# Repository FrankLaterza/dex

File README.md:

# Dex
An open source self balancing robot designed for the Raspberry Pi Pico and controlled by a DS4 controller. Dex was made with 3D printed ABS, a custom PCB, and a whole lot of patience. This repository shall serve as a reference for anyone making their own balancing robot. The code is well formatted for your convenience you nerd. Note this is an intermediate project so take your time and have fun.

<div style="display:flex; justify-content:center;">
  
</div>
<br/>

## Software
This project uses the several libraries including FreeRTOS, BTstack, and the Pico SDK. Each is a specific versions and can be setup with a recursive git clone. For this project the software utilizes both cores on the RP2040.
_
### Core 0
The primary purpose of core 0 is to handle all of the CWY43 SPI and MPU6050 I2C interrupts that hog all the cpu.

### Core 1
The FreeRTOS scheduler runs on this core to prevent conflicting timing with the SPI interrupted. The bluetooth callback also gets processed here. 

| FreeRTOS Scheduler Tasks | Description | Task Delay us |
| ----- | ---- | ---- |
| stat_led_task | blinky blinky | 500000us |
| bt_hid_inputs | process controller inputs | 20000us |
| stepper_left_task | controls the left stepper | varying per step |
| stepper_right_task | controls the right stepper | varying per step  |
| mpu6050_task | requests gyro/accelerometer data and processed roll angle with Kalman filter | 20000us |
| pid_task | calculates the output for the stepper motors | 10000us |
| good_boy_task | watches the dog | 500000us |

### Overclocking
Please note this project overclock the RP2040 to 250MHz and configures the configTICK_RATE_HZ 100000 (10us period). This is to give enough time for the schedule overhead. The reason for the high tick rate is because the steppers need step at very high rates.

## PCB 
This PCB was made in Eagle Cad and can find the PCB under resources/pcb. Please note there are two mistakes that i've hand wired for this current pcb. The holes for the switch are too small and cut traces to make the switch come before the 5V regulator. I'll update the files with a fixed design soon.

<div style="display:flex; justify-content:center;">
  
</div>

## CAD
This project was designed in Fusion 360 and all the files can be found under resources/cad. 
<div style="display:flex; justify-content:center;">
  
</div>

## BOM 💣

| Name                    | Count | Price (meets count) | Description                               | Rating                   | Notes                                        | Link                                                                                                                             |
|-------------------------|-------|----------------------|-------------------------------------------|--------------------------|----------------------------------------------|-----------------------------------------------------------------------------------------------------------------------------------|
| Raspberry Pi PIco W      | 1     | $18.96               | MPU                                       | Clock: 135MHz            | 2 Cores                                      | [Amazon Link](https://www.amazon.com/gp/product/B0B72GV3K3/ref=ewc_pr_img_12?smid=A1PI3LRUETBKN8&psc=1)                            |
| PCB                     | 1     | $24.05               | Custom PCB designed                        | Engineering Level: Maximum | Designed in Eagle and order on JLCPCB        | N/A                                                                                                                               |
| NEMA 17 Stepper         | 2     | $13.99               | Main Motors                                | Max Current 2a           |                                              | [Amazon Link](https://www.amazon.com/gp/product/B0B72GV3K3/ref=ewc_pr_img_12?smid=A1PI3LRUETBKN8&psc=1)                            |
| Stepper Driver A4988    | 2     | $14.99               | Drives the stepper motors                  | Min Step Rate: 500kHz    |                                              | [Amazon Link](https://www.amazon.com/gp/product/B09X382335/ref=ewc_pr_img_2?smid=A1VTL661FOEJB1&th=1)                            |
| MPU-6050                | 1     | $7.59                | 3 Axis Gryo and Accelerometer               | 16bit                    |                                              | [Amazon Link](https://www.amazon.com/gp/product/B0B3D6D1KD/ref=ppx_yo_dt_b_search_asin_title?ie=UTF8&psc=1)                      |
| L7805CV                 | 1     | $8.59                | 5V Voltage Regulator                       | 35Vin and 5Vout/1.5A     |                                              | [Amazon Link](https://www.amazon.com/gp/product/B0CBKCDT4H/ref=ewc_pr_img_1?smid=A3FX7C4A9P37IQ&th=1)                             |
| Power Switch            | 1     | $6.99                | AC 125V 2A                                 |                          | Only cuts power 5V power not stepper input voltage | [Amazon Link](https://www.amazon.com/gp/product/B099N61GTZ/ref=ewc_pr_img_3?smid=A3KX1QBS9AS0L7&th=1)                              |
| LED                     | 4     | $11.99               |                                           | Forward Voltage: R/Y 2.0-2.2V; B/G/W 3.0-3.2V; Max. Current: 20mA | User about 100Ohm resistor                | [Amazon Link](https://www.amazon.com/DiCUNO-450pcs-Colors-Emitting-Assorted/dp/B073QMYKDM/ref=sr_1_3?crid=25RYXUCKOI5YQ&keywords=led+5mm&qid=1702651386&s=hi&sprefix=led+5mm%2Ctools%2C109&sr=1-3) |
| Beeper                  | 1     | $7.99                | Active beeeper                             | 2.5-4V/25mA.             | Make sure to be extra annoying                   | [Amazon Link](https://www.amazon.com/gp/product/B07VRK7ZPF/ref=ewc_pr_img_5?smid=A10PG8DP5LW0Q1&psc=1)                           |
| Resistors               | 4     | $5.99                | Resistor for LEDS                          |                          |                                              | [Amazon Link](https://www.amazon.com/MCIGICM-Values-Resistor-Assortment-Resistors/dp/B06WRQS97C/ref=sr_1_3?crid=1DUTLH3JED9NZ&keywords=resistor+pack&qid=1702651595&s=electronics&sprefix=resistor+pack%2Celectronics%2C136&sr=1-3) |
| Headers                 | N/A   | $7.99                | Used for PCB and IO                        |                          |                                              | [Amazon Link](https://www.amazon.com/2-54mm-Breakaway-Female-Connector-Arduino/dp/B01MQ48T2V/ref=sr_1_3?crid=3A3SUEBT5HOUP&keywords=headers%2Bmale%2Band%2Bfemale&qid=1702651771&sprefix=headers%2Bmale%2Band%2Bfemail%2B%2Caps%2C112&sr=8-3&th=1) |
| Battery                 | 1     | $44.99               | Any 4s Lipo will work                     | 4S Lipo Battery 5200mAh 14.8V 60C |                                              | [Amazon Link](https://www.amazon.com/Pairs-Connector-Female-Silicon-Battery/dp/B07QM1WS2J/ref=sr_1_6?crid=2MAGLONAR29QX&keywords=Dean+t+plug&qid=1702651946&s=toys-and-games&sprefix=dean+t+plu%2Ctoys-and-games%2C98&sr=1-6) |
| O rings                 | 2     | $5.99                | Goes over 3d printed wheel for grip        | 110mm OD 100mm ID 5mm Width | I used the wheels from Wouter [here](https://elexperiment.nl/2018/11/high-speed-balancing-robot-introduction/)             | [Amazon Link](https://www.amazon.com/gp/product/B07GXFKGNT/ref=ppx_yo_dt_b_search_asin_title?ie=UTF8&th=1)                       |
| 3D Printed Chassis       | 1     | 0                    | Main body of the robot                     |                          | Designed in Fusion 360                         | N/A                                                                |
| 3D printed Wheels       | 2     | 0                    | Main wheels with rubber O rings            | Designed in Fusion 360 CREDIT DESIGN |                                           | N/A                                                            |

## Known Issues
* Sometimes the program will halt when trying to connect to the BT HID.
* Cannot reconnect to pico after pair to another controller.

## Starting Debugger
Plug in debugger and run:
```
openocd -f interface/cmsis-dap.cfg -c "adapter speed 5000" -f target/rp2040.cfg -s tcl
```
confrim this starts on localhost:3333

open another terminal and run:
```
gdb-multiarch dex.elf
```
in this termincal type the command
```
target remote localhost:3333
```
load with 
```
load
```

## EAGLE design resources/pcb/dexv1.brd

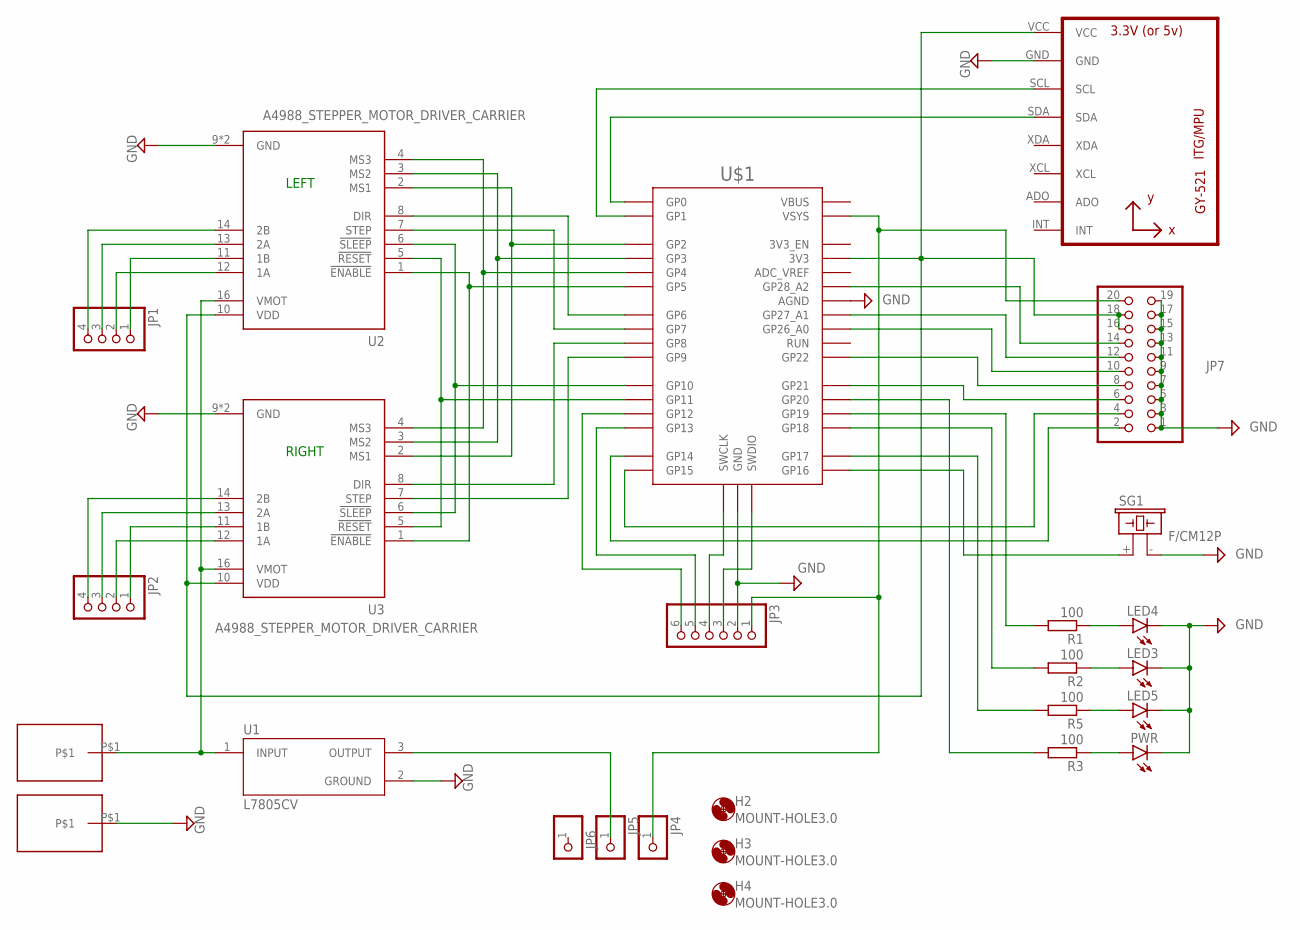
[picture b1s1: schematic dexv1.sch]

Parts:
H2, H3, H4: MOUNT-HOLE3.0; 3,0
JP1, JP2: PINHD-1X4; 1X04
JP3: PINHD-1X6; 1X06
JP4, JP5, JP6: PINHD-1X1; 1X01
JP7: PINHD-2X10; 2X10
LED3, LED4, LED5: LED5MM
PWR: LED5MM
R1, R2, R3, R5: 100; 0204/7
SG1: F/CM12P
U1: L7805CV; TO255P1040X460X1968-3
U2, U3: A4988_STEPPER_MOTOR_DRIVER_CARRIER; MODULE_A4988_STEPPER_MOTOR_DRIVER_CARRIER
U4: GY-521MPU6050; GY-521
U$1: RPI_PICO-TH; RPI_PICO_TH
U$2, U$3: SMD5X10

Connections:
GND: JP3.2, JP7.1, JP7.3, JP7.5, JP7.7, JP7.9, JP7.11, JP7.13, JP7.15, JP7.17, JP7.19, LED3.K (C), LED4.K (C), LED5.K (C), PWR.K (C), SG1.- (2), U1.2 (GROUND), U2.9 (GND), U2.15 (GND), U3.9 (GND), U3.15 (GND), U4.GND, U$1.AGND, U$1.GND@1 (GND), U$1.GND@2 (GND), U$1.GND@3 (GND), U$1.GND@4 (GND), U$1.GND@5 (GND), U$1.GND@6 (GND), U$1.GND@7 (GND), U$1.GND@8 (GND), U$1.P$2 (GND), U$3.P$1
unnamed: JP2.2, U3.12 (1A)
unnamed: U4.SDA, U$1.GP0
unnamed: JP7.14, U$1.GP28_A2
unnamed: U2.4 (MS3), U3.4 (MS3), U$1.GP4
unnamed: U2.3 (MS2), U3.3 (MS2), U$1.GP3
unnamed: U2.2 (MS1), U3.2 (MS1), U$1.GP2
unnamed: U2.8 (DIR), U$1.GP6
unnamed: U2.7 (STEP), U$1.GP7
unnamed: U3.8 (DIR), U$1.GP8
unnamed: U2.1 (!ENABLE), U3.1 (!ENABLE), U$1.GP5
unnamed: U3.7 (STEP), U$1.GP9
unnamed: U2.6 (!SLEEP), U3.6 (!SLEEP), U$1.GP10
unnamed: U2.5 (!RESET), U3.5 (!RESET), U$1.GP11
unnamed: JP1.2, U2.12 (1A)
unnamed: JP1.1, U2.11 (1B)
unnamed: JP1.3, U2.13 (2A)
unnamed: JP1.4, U2.14 (2B)
unnamed: JP2.1, U3.11 (1B)
unnamed: JP2.3, U3.13 (2A)
unnamed: JP2.4, U3.14 (2B)
unnamed: JP3.1, JP4.1, JP7.20, U$1.VSYS
unnamed: JP5.1, U1.3 (OUTPUT)
unnamed: JP7.4, U$1.GP15
unnamed: SG1.+ (1), U$1.GP16
unnamed: U4.SCL, U$1.GP1
unnamed: LED4.A, R1.1
unnamed: LED3.A, R2.1
unnamed: R5.2, U$1.GP17
unnamed: LED5.A, R5.1
unnamed: JP3.6, U$1.GP12
unnamed: JP3.3, U$1.P$3 (SWDIO), U$1.SWDIO
unnamed: JP3.4, U$1.P$1 (SWCLK), U$1.SWCLK
unnamed: JP3.5, U$1.GP13
unnamed: JP7.10, U$1.GP26_A0
unnamed: R1.2, U$1.GP19
unnamed: R2.2, U$1.GP18
unnamed: JP7.12, U$1.GP27_A1
unnamed: JP7.8, U$1.GP22
unnamed: JP7.6, U$1.GP21
unnamed: U1.1 (INPUT), U2.16 (VMOT), U3.16 (VMOT), U$2.P$1
unnamed: JP7.16, JP7.18, U2.10 (VDD), U3.10 (VDD), U4.VCC, U$1.3V3
unnamed: JP7.2, U$1.GP14
unnamed: PWR.A, R3.1
unnamed: R3.2, U$1.GP20

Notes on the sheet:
LEFT
RIGHT

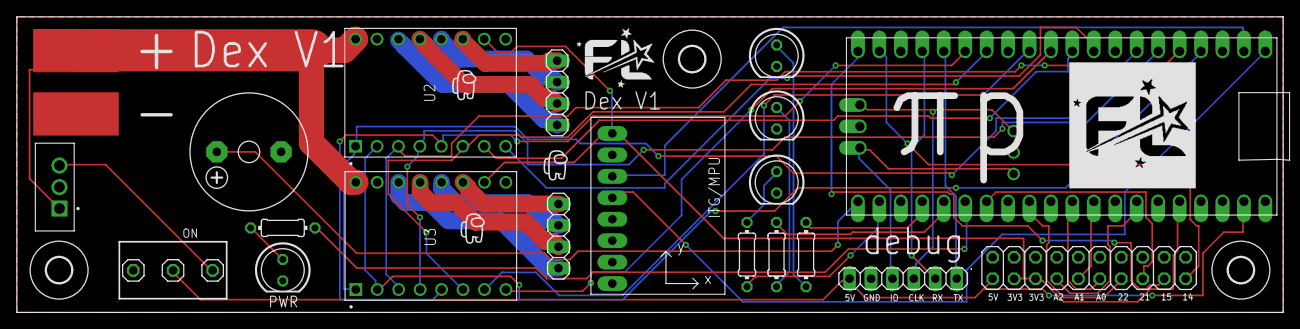
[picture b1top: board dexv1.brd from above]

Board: 2 copper layers, 150.0 x 35.0 mm, 26 parts (0 on the bottom side), 45 nets.

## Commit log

2023-12-22 setup
2023-12-22 btstack hash
2023-12-22 pico-sdk hash
2023-12-22 FreeRTOS-Kernel
2023-12-26 working bt
2023-12-30 added mpu6050
2023-12-30 maintenance
2023-12-31 stepper wip
2024-01-01 overclock
2024-01-01 balance
2024-01-04 control profile
2024-01-07 rpm target
2024-01-08 tweaker
2024-01-10 joystick config
2024-01-14 blance control wip
2024-01-14 tuned
2024-01-15 readme
2024-01-19 underclock
